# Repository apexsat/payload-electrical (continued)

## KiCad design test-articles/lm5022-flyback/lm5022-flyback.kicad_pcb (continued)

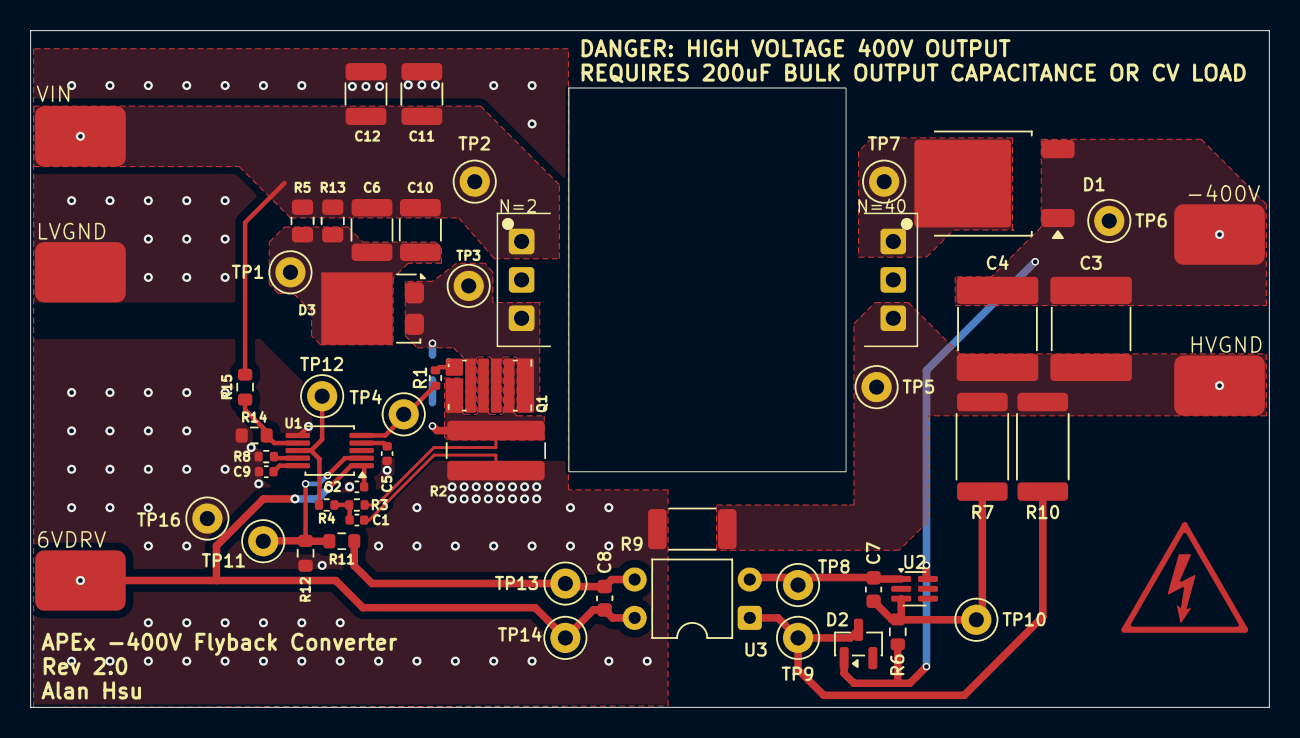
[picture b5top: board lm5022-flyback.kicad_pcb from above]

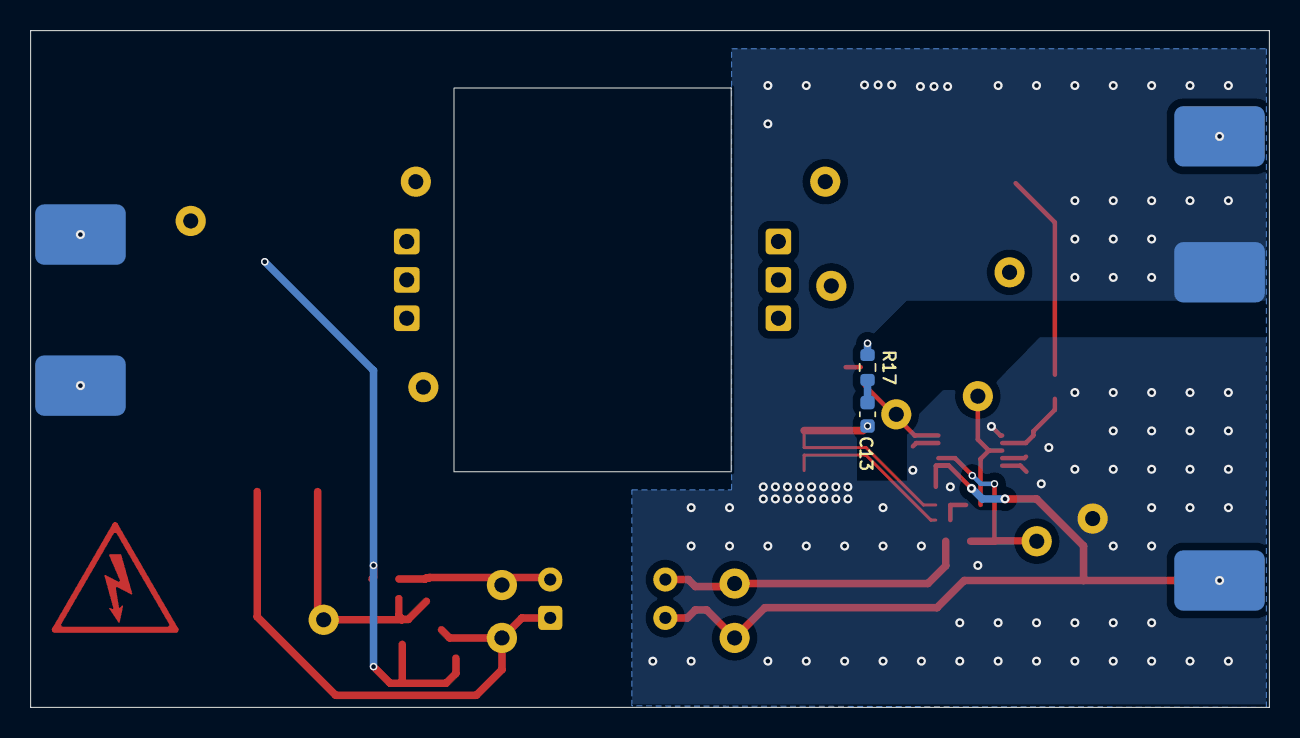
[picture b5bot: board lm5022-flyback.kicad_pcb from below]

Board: 2 copper layers, 82.0 x 44.8 mm, 57 parts (2 on the bottom side), 23 nets.

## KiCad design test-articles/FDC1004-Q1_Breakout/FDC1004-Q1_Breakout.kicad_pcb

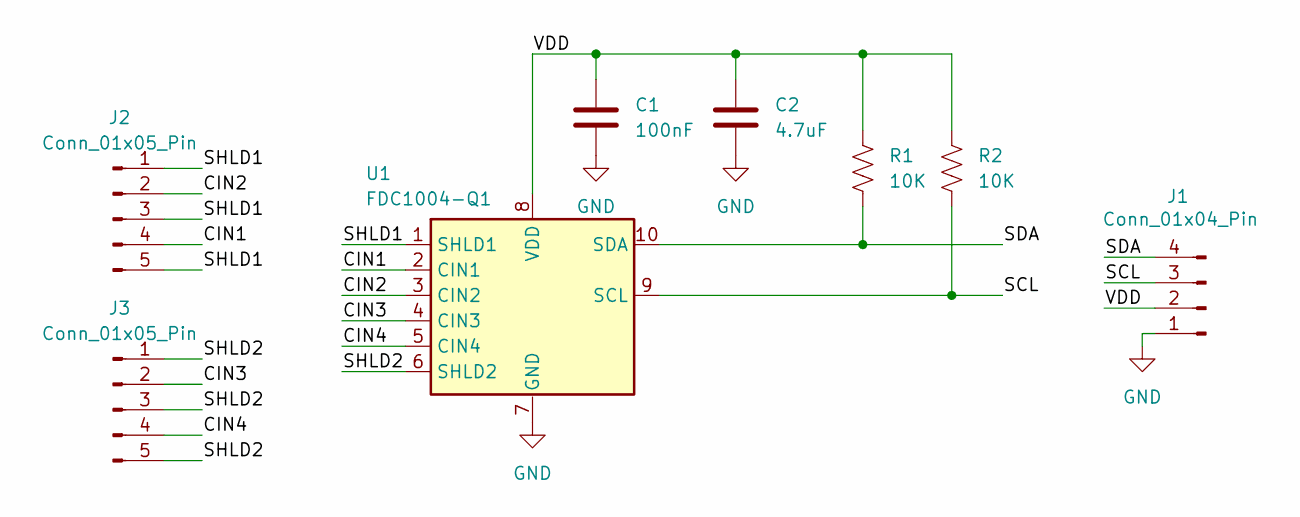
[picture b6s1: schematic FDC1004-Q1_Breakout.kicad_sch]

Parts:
C1: 100nF; C_0805_2012Metric_Pad1.18x1.45mm_HandSolder
C2: 4.7uF; C_0805_2012Metric_Pad1.18x1.45mm_HandSolder
J1: Conn_01x04_Pin; PinHeader_1x04_P2.54mm_Vertical
J2, J3: Conn_01x05_Pin; PinHeader_1x05_P2.54mm_Vertical
R1, R2: 10K; R_0805_2012Metric_Pad1.20x1.40mm_HandSolder
U1: FDC1004-Q1; VSSOP-10_3x3mm_P0.5mm

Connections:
/CIN1: J2.4, U1.2 (CIN1)
/CIN2: J2.2, U1.3 (CIN2)
/CIN3: J3.2, U1.4 (CIN3)
/CIN4: J3.4, U1.5 (CIN4)
/SCL: J1.3, R2.2, U1.9 (SCL)
/SDA: J1.4, R1.2, U1.10 (SDA)
/SHLD1: J2.1, J2.3, J2.5, U1.1 (SHLD1)
/SHLD2: J3.1, J3.3, J3.5, U1.6 (SHLD2)
/VDD: C1.1, C2.1, J1.2, R1.1, R2.1, U1.8 (VDD)
GND: C1.2, C2.2, J1.1, U1.7 (GND)

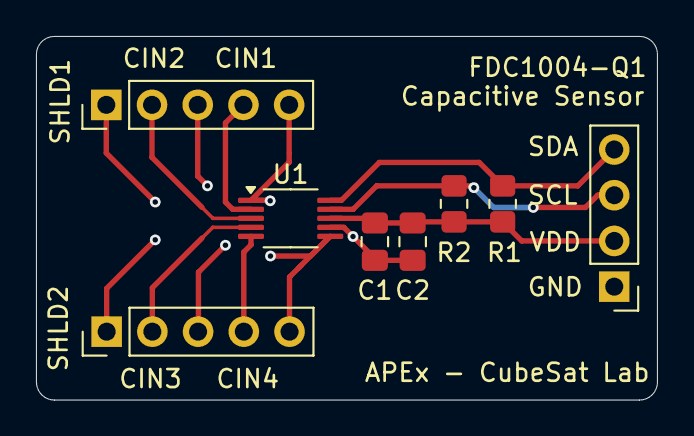
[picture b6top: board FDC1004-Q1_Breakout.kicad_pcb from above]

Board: 2 copper layers, 34.5 x 20.2 mm, 8 parts (0 on the bottom side), 10 nets.

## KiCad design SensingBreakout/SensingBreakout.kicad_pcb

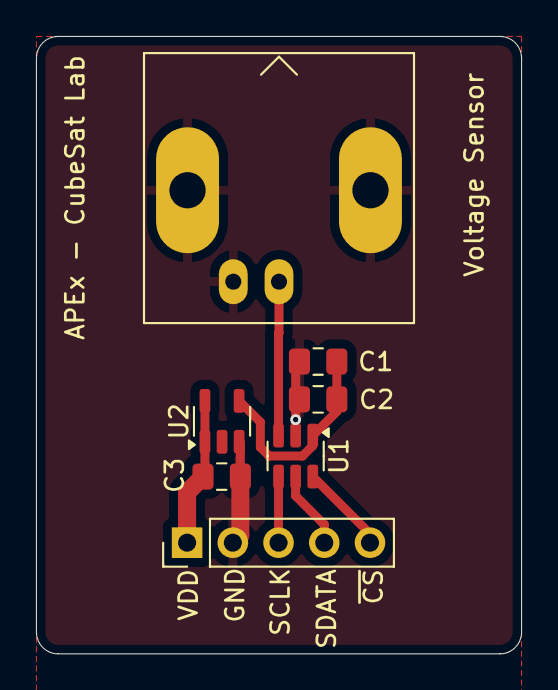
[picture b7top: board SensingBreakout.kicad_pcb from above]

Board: 2 copper layers, 27.0 x 34.3 mm, 7 parts (0 on the bottom side), 7 nets.

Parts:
C1, C3: 4.7uF; C_0805_2012Metric_Pad1.18x1.45mm_HandSolder
C2: 100nF; C_0805_2012Metric_Pad1.18x1.45mm_HandSolder
J1: Conn_BNC; BNC_Amphenol_B6252HB-NPP3G-50_Horizontal
J2: Conn_01x05_Pin; PinHeader_1x05_P2.54mm_Vertical
U1: ADCS7476; SOT-23-6
U2: TC1016-3.3V; TSOT-23-5

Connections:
/SCLK: J2.3, U1.4 (SCLK)
/SDATA: J2.4, U1.5 (SDATA)
/VDD: C3.1, J2.1, U2.1 (~SHDN), U2.5 (VIN)
/~CS: J2.5, U1.6 (~CS)
GND: C1.2, C2.2, C3.2, J1.2 (Ext), J2.2, U1.2 (GND), U2.3 (GND)
unnamed: J1.1 (In), U1.3 (VIN)
unnamed: C1.1, C2.1, U1.1 (VDD), U2.4 (VOUT)

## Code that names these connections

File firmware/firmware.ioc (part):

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Mcu.Name=STM32G431R(6-8-B)Tx
Mcu.Package=LQFP64
Mcu.UserName=STM32G431RBTx
PA0.Mode=IN1-Single-Ended
PA0.Signal=ADC1_IN1
PA1.Mode=IN2-Single-Ended
PA1.Signal=ADC2_IN2
PA10.GPIOParameters=GPIO_Label
PA10.GPIO_Label=VBAT_EN
PA10.Signal=GPIO_Output
PA11.GPIOParameters=GPIO_Label
PA11.GPIO_Label=VBAT_PGOOD
PA11.Signal=GPIO_Input
PA12.GPIOParameters=GPIO_Label
PA12.GPIO_Label=PD_RST
PA12.Signal=GPIO_Output
PA13.Mode=Serial_Wire
PA13.Signal=SYS_JTMS-SWDIO
PA14.Mode=Serial_Wire
PA14.Signal=SYS_JTCK-SWCLK
PA15.GPIOParameters=GPIO_Label
PA15.GPIO_Label=DPT_TANK_FRIT_SEL
PA15.Signal=GPIO_Output
PA2.GPIOParameters=GPIO_Label
PA2.GPIO_Label=PGOOD_12V
PA2.Signal=GPIO_Input
PA3.Mode=IN4-Single-Ended
PA3.Signal=ADC1_IN4
PA4.Mode=NSS_Signal_Hard_Input
PA4.Signal=SPI1_NSS
PA5.Mode=Full_Duplex_Slave
PA5.Signal=SPI1_SCK
PA6.Mode=Full_Duplex_Slave
PA6.Signal=SPI1_MISO
PA7.Mode=Full_Duplex_Slave
PA7.Signal=SPI1_MOSI
PA8.Mode=I2C
PA8.Signal=I2C2_SDA
PA9.Mode=I2C
PA9.Signal=I2C2_SCL
PB0.Mode=IN15-Single-Ended
PB0.Signal=ADC1_IN15
PB1.Mode=IN12-Single-Ended
PB1.Signal=ADC1_IN12
PB10.GPIOParameters=GPIO_Label
PB10.GPIO_Label=HTR2_EN
PB10.Signal=GPIO_Output
PB11.Mode=IN14-Single-Ended
PB11.Signal=ADC1_IN14
PB12.Mode=IN11-Single-Ended
PB12.Signal=ADC1_IN11
PB13.GPIOParameters=GPIO_Label
PB13.GPIO_Label=DISCHARGE_EN
PB13.Signal=GPIO_Output
PB14.Mode=IN5-Single-Ended
PB14.Signal=ADC1_IN5
PB15.GPIOParameters=GPIO_Label
PB15.GPIO_Label=IGNITER_EN
PB15.Signal=GPIO_Output
PB2.GPIOParameters=GPIO_Label
PB2.GPIO_Label=WDG_IN
PB2.Signal=GPIO_Output
PB3.GPIOParameters=GPIO_Label
PB3.GPIO_Label=VALVE1_L
PB3.Signal=GPIO_Output
PB4.GPIOParameters=GPIO_Label
PB4.GPIO_Label=VALVE1_H
PB4.Signal=GPIO_Output
PB5.GPIOParameters=GPIO_Label
PB5.GPIO_Label=VALVE2_EN
PB5.Signal=GPIO_Output
PB6.GPIOParameters=GPIO_Label
PB6.GPIO_Label=VALVE3_L
PB6.Signal=GPIO_Output
PB7.GPIOParameters=GPIO_Label
PB7.GPIO_Label=VALVE3_H
PB7.Signal=GPIO_Output
PB9.GPIOParameters=GPIO_Label
PB9.GPIO_Label=HTR1_EN
PB9.Signal=GPIO_Output
PC0.Mode=Asynchronous
PC0.Signal=LPUART1_RX
PC1.Mode=Asynchronous
PC1.Signal=LPUART1_TX
PC10.GPIOParameters=GPIO_Label
PC10.GPIO_Label=DPT_SCK
PC10.Signal=GPIO_Output
PC11.GPIOParameters=GPIO_Label
PC11.GPIO_Label=DPT_MISO
PC11.Signal=GPIO_Input
PC12.GPIOParameters=GPIO_Label
PC12.GPIO_Label=DPT_MOSI
PC12.Signal=GPIO_Output
PC13.GPIOParameters=GPIO_Label
PC13.GPIO_Label=DISCHARGE_PGOOD
PC13.Signal=GPIO_Input
PC14-OSC32_IN.GPIOParameters=GPIO_Label
PC14-OSC32_IN.GPIO_Label=IGNITER_PGOOD
PC14-OSC32_IN.Signal=GPIO_Input
PC2.Mode=IN8-Single-Ended
PC2.Signal=ADC1_IN8
PC3.Mode=IN9-Single-Ended
PC3.Signal=ADC1_IN9
PC4.GPIOParameters=GPIO_Label
PC4.GPIO_Label=DRDY
PC4.Signal=GPIO_Output
PC5.GPIOParameters=GPIO_Label
PC5.GPIO_Label=ARM/SAFE
PC5.Signal=GPIO_Output
PC6.GPIOParameters=GPIO_Label
PC6.GPIO_Label=IGNITER_PULSE
PC6.Signal=GPIO_Output
PC7.Signal=S_TIM3_CH2
PC8.Mode=I2C
PC8.Signal=I2C3_SCL
PC9.Mode=I2C
PC9.Signal=I2C3_SDA
PD2.GPIOParameters=GPIO_Label
PD2.GPIO_Label=DEBUG_LED
PD2.Signal=GPIO_Output
PF0-OSC_IN.Mode=HSE-External-Oscillator
PF0-OSC_IN.Signal=RCC_OSC_IN
PF1-OSC_OUT.Mode=HSE-External-Oscillator
PF1-OSC_OUT.Signal=RCC_OSC_OUT
RCC.HSE_VALUE=8000000
RCC.SYSCLKFreq_VALUE=64000000
RCC.SYSCLKSource=RCC_SYSCLKSOURCE_PLLCLK
board=custom

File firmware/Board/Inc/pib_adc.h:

#ifndef PIB_ADC_H
#define PIB_ADC_H

#include "stm32g4xx_hal.h"
#include <stdbool.h>

/*
 * PIB (200_40) analog inputs on ADC1 + ADC2.
 *
 *  - Burst: ADC_V_DCHG (PA0, ADC1_IN1) + ADC_I_DCHG (PA1, ADC2_IN2) on the
 *    regular group, dual regular-simultaneous, DMA one-shot, 2.133 MSPS per
 *    channel. Configured by CubeMX (firmware.ioc).
 *  - Housekeeping: every other channel, read through the ADC1 injected group.
 *    This driver replaces the CubeMX injected setup at init.
 *
 * Sample times and channel map: 200_40 PIB/PIB_Schematic_Review.md,
 * "ADC configuration" section.
 *
 * Only one pib_adc_t may be initialised (the HAL ADC callbacks are global).
 */

/* ---- Housekeeping channels ------------------------------------------------ */

/* Order sets the injected sequence: 4 channels per sequence, in this order. */
typedef enum {
    HK_VREFINT = 0,     /* internal reference, used to measure VDDA */
    HK_TEMP_MCU,        /* internal temperature sensor              */
    HK_NTC_PIB,
    HK_TANK_NTC_1,
    HK_TANK_NTC_2,
    HK_NTC_DCHG,
    HK_NTC_IGN,
    HK_V_IGN_SUPPLY,
    HK_V_IGN_PK,
    HK_I_IGN_PK,
    HK_NUM_CH
} hk_ch_t;

/* ADC1 channel for each signal (from the 200_40 PIB schematic).
   These must match the pin assignments in firmware.ioc. */
#define HK_ADC_CH_VREFINT       ADC_CHANNEL_VREFINT
#define HK_ADC_CH_TEMP_MCU      ADC_CHANNEL_TEMPSENSOR_ADC1
#define HK_ADC_CH_NTC_PIB       ADC_CHANNEL_12   /* PB1  ADC_NTC_PIB        */
#define HK_ADC_CH_TANK_NTC_1    ADC_CHANNEL_14   /* PB11 ADC_TANK_NTC_1     */
#define HK_ADC_CH_TANK_NTC_2    ADC_CHANNEL_15   /* PB0  ADC_TANK_NTC_2     */
#define HK_ADC_CH_NTC_DCHG      ADC_CHANNEL_11   /* PB12 ADC_NTC_DCHG       */
#define HK_ADC_CH_NTC_IGN       ADC_CHANNEL_9    /* PC3  ADC_NTC_IGN        */
#define HK_ADC_CH_V_IGN_SUPPLY  ADC_CHANNEL_4    /* PA3  ADC_V_IGN_SUPPLY_C */
#define HK_ADC_CH_V_IGN_PK      ADC_CHANNEL_5    /* PB14 ADC_V_IGN_PK_C     */
#define HK_ADC_CH_I_IGN_PK      ADC_CHANNEL_8    /* PC2  ADC_I_IGN_PK_C     */

/* Sample time per channel. ADC clk = HCLK/2 = 32 MHz.
   Igniter channels (1k series + BAT54J clamps) need >= 47.5 cycles
   (DS12589 Table 61, R_AIN <= 1.8k on slow channels); 92.5 also covers
   series resistance on the igniter board. NTC channels have 100 nF at the
   pin, so 92.5 is a uniform default there, not a requirement. */
#define HK_SMP_VREFINT          ADC_SAMPLETIME_247CYCLES_5  /* 7.7 us, needs >= 4 us (DS12589 Table 20) */
#define HK_SMP_TEMP_MCU         ADC_SAMPLETIME_247CYCLES_5  /* 7.7 us, needs >= 5 us (DS12589 Table 75) */
#define HK_SMP_NTC_PIB          ADC_SAMPLETIME_92CYCLES_5   /* 2.9 us, R109 10k / TH1, C76 100 nF       */
#define HK_SMP_TANK_NTC_1       ADC_SAMPLETIME_92CYCLES_5   /* 2.9 us, R4 22k bias, C19 100 nF          */
#define HK_SMP_TANK_NTC_2       ADC_SAMPLETIME_92CYCLES_5   /* 2.9 us, R3 22k bias, C20 100 nF          */
#define HK_SMP_NTC_DCHG         ADC_SAMPLETIME_92CYCLES_5   /* 2.9 us, R87 10k bias, C61 100 nF         */
#define HK_SMP_NTC_IGN          ADC_SAMPLETIME_92CYCLES_5   /* 2.9 us, R78 10k bias, C44 100 nF         */
#define HK_SMP_V_IGN_SUPPLY     ADC_SAMPLETIME_92CYCLES_5   /* 2.9 us, R129 1k series, no pin cap       */
#define HK_SMP_V_IGN_PK         ADC_SAMPLETIME_92CYCLES_5   /* 2.9 us, R131 1k series, no pin cap       */
#define HK_SMP_I_IGN_PK         ADC_SAMPLETIME_92CYCLES_5   /* 2.9 us, R130 1k series, no pin cap       */

#define HK_INJ_MAX_RANKS   4U   /* hardware limit of the injected sequencer */
#define HK_NUM_SEQ         ((HK_NUM_CH + HK_INJ_MAX_RANKS - 1U) / HK_INJ_MAX_RANKS)

typedef struct {
    uint16_t raw[HK_NUM_CH];   /* 12-bit counts, indexed by hk_ch_t          */
    uint32_t mv[HK_NUM_CH];    /* pin voltage in mV, scaled by measured VDDA */
    uint32_t vdda_mv;          /* from VREFINT + factory VREFINT_CAL         */
    int32_t  temp_mcu_degC;    /* from TS_CAL1/TS_CAL2                       */
} hk_adc_t;

/* ---- Discharge burst ------------------------------------------------------ */

/* Unpack one burst word (DMA access mode 12/10-bit):
   ADC1 master = V_DCHG in [15:0], ADC2 slave = I_DCHG in [31:16]. */
#define ADC_BURST_V_RAW(word)   ((uint16_t)((word) & 0xFFFFU))
#define ADC_BURST_I_RAW(word)   ((uint16_t)((word) >> 16))

typedef enum {
    ADC_BURST_IDLE = 0,
    ADC_BURST_RUNNING,   /* DMA filling the buffer                       */
    ADC_BURST_CAPTURED,  /* buffer full, post-burst VREFINT not read yet */
    ADC_BURST_DONE,      /* buffer full, vdda_after_mv valid             */
    ADC_BURST_ERROR
} adc_burst_state_t;

typedef struct {
    volatile adc_burst_state_t state;
    uint32_t *buf;             /* caller-owned, one V/I pair per word */
    uint32_t  n_samples;
    uint32_t  vdda_before_mv;  /* VREFINT read just before the burst  */
    uint32_t  vdda_after_mv;   /* VREFINT read just after the burst   */
} adc_burst_t;

/* ---- Driver instance ------------------------------------------------------ */

typedef struct {
    ADC_HandleTypeDef *master;   /* ADC1: V_DCHG + injected housekeeping */
    ADC_HandleTypeDef *slave;    /* ADC2: I_DCHG                         */

    volatile hk_adc_t hk;        /* latest housekeeping results          */
    adc_burst_t       burst;     /* current / last burst                 */

    /* JSQR value for each injected sequence, captured at init */
    uint32_t jsqr_hk[HK_NUM_SEQ];
    uint32_t jsqr_vrefint;
} pib_adc_t;

/* Call once after MX_ADC1_Init()/MX_ADC2_Init(), before any ADC use.
   Calibrates both ADCs and builds the injected sequences. */
HAL_StatusTypeDef pib_adc_init(pib_adc_t *adc, ADC_HandleTypeDef *master, ADC_HandleTypeDef *slave);

/* Read every housekeeping channel once into adc->hk (~45 us, blocking).
   Returns HAL_BUSY while a burst is running. */
HAL_StatusTypeDef pib_adc_read_housekeeping(pib_adc_t *adc);

/* Start a burst into buf (n_samples words, max 65535). Returns at once. */
HAL_StatusTypeDef pib_adc_burst_start(pib_adc_t *adc, uint32_t *buf, uint32_t n_samples);

/* Non-blocking; call from thread context until DONE or ERROR. */
adc_burst_state_t pib_adc_burst_poll(pib_adc_t *adc);

/* Blocking: start a burst and wait for it (timeout_ms >= 2). */
HAL_StatusTypeDef pib_adc_burst_read(pib_adc_t *adc, uint32_t *buf, uint32_t n_samples,
                                     uint32_t timeout_ms);

/* Stop a running burst. Leaves the ADCs enabled. */
void pib_adc_burst_abort(pib_adc_t *adc);

uint32_t pib_adc_burst_count(pib_adc_t *adc);

uint32_t pib_adc_burst_sync(pib_adc_t *adc, uint32_t min_count, uint32_t *cycles);

#endif /* PIB_ADC_H */

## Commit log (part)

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2026-02-25 Uploading Planar Transformer Project
2026-02-26 lm5022 pcb
2026-02-28 This FDC1004-Q1 Breakout board
2026-02-28 PIB Sensing Board
2026-02-28 Typo
2026-03-02 FDC1004-Q1 Gerbers
2026-03-02 lm5022 work
2026-03-02 add CSA to lm5022
2026-03-06 TID Testing Board Initial Draft Complete
2026-03-09 ADC Tester
2026-03-10 add matlab simulation
2026-03-10 opto design feedback
2026-03-11 progress on flyback
2026-03-19 update sim and finish high level sch for flyback
2026-03-22 footprint assignment for flyback
2026-03-23 layout work
2026-03-23 finish layout
2026-03-23 update EPC2302 3dmodel
2026-03-23 Flyback Rev 1.0 release
2026-03-23 adc testing move to v9
2026-03-31 overhaul the simulation so its actually correct in DCM
2026-04-07 euler work
2026-04-07 fix euler and find out nothing was wrong
2026-04-07 rev 2 of 400V converter
2026-04-08 v2 converter
2026-04-17 updated values
